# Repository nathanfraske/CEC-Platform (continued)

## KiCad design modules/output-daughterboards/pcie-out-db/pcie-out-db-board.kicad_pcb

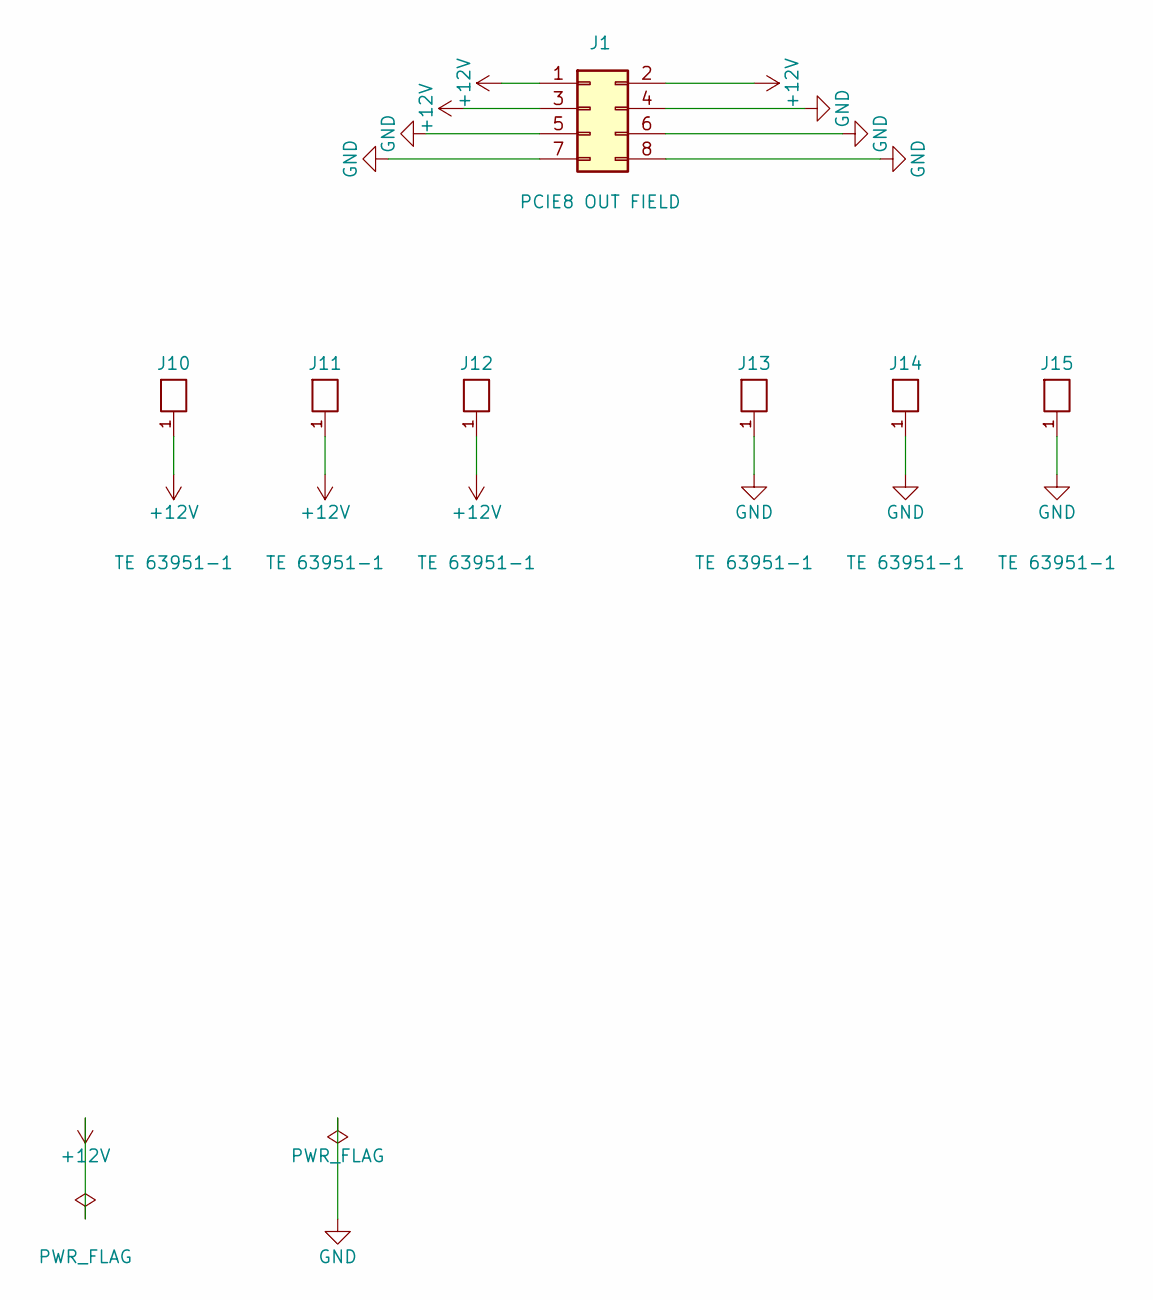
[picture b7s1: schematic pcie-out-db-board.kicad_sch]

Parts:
J1: PCIE8 OUT FIELD; PCIe8_Daughterboard_Field_P4.20mm
J10, J11, J12, J13, J14, J15: TE 63951-1; TE_63951-1_FASTON_Tab_250x032_RA_THT; MPN 63951-1; LCSC C591344

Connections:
+12V: J1.1, J1.2, J1.3, J10.1, J11.1, J12.1
GND: J1.4, J1.5, J1.6, J1.7, J1.8, J13.1, J14.1, J15.1

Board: 4 copper layers, 7 parts (0 on the bottom side), 2 nets, no tracks yet.

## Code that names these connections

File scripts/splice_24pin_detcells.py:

#!/usr/bin/env python3
# One-shot splice: add INA181A2 + TLV7011 fast-detection cells on the 24-pin's
# 3V3 and 5VSB rails, so all four rails carry the §6.13-style detection front end
# (owner 2026-07-07: "add the INA181 + comparator to the two remaining rails ...
# we are a total monitor anyway"). Mirrors the existing 12V/5V cells exactly
# (INA181A2 amp taps the same shunt Kelvin pair -> TLV7011 comparator vs the
# board-shared /THRESH -> a free MCU GPIO). Label-driven, like the flat sheet.
# Idempotent-guarded: refuses to run if the new refs already exist.
import sys, os, re
HERE = os.path.dirname(os.path.abspath(__file__))
sys.path.insert(0, HERE)
import cec_sch

SCH = os.path.join(HERE, "..", "modules", "atx-24pin-rev3", "24pin-module.kicad_sch")
PROJECT = "24pin-module"
ROOT = "a4774022-41d4-4be7-85b6-fed5477a3f9f"
GRID = 1.27

txt = open(SCH).read()

# ---- IC pin local geometry, carved from the file's own lib_symbols cache ----
def carve(t, i):
    d = 0
    for j in range(i, len(t)):
        if t[j] == '(':
            d += 1
        elif t[j] == ')':
            d -= 1
            if d == 0:
                return t[i:j+1]
    return None

def pins_of(libname):
    m = re.search(r'\(symbol "' + re.escape(libname) + r'"', txt)
    return cec_sch.pin_table(carve(txt, m.start()))

PIN = {
    "INA181": pins_of("cec-vendor:INA181A2IDBVR"),
    "TLV":    pins_of("cec-vendor:TLV7011DBVR"),
    "C":      pins_of("cec-vendor:C_Small"),
    "MCU":    pins_of("cec-vendor:ESP32-C6-MINI-1-N4"),
}

# ---- refs / placement ----
# Two cells, continuing the amp(x=294.64)/comp(x=364.49) column below the 5V cell.
CELLS = [
    dict(rail="3V3",  y=142.24, amp="U63V31",  comp="U73V31",  cap="C63V31",
         hi="SENSE3V3_HI",  lo="SENSE3V3_LO",  detamp="DETAMP3V3",  det="DET3V3",  mcu_pin="15"),
    dict(rail="5VSB", y=161.29, amp="U65VSB1", comp="U75VSB1", cap="C65VSB1",
         hi="SENSE5VSB_HI", lo="SENSE5VSB_LO", detamp="DETAMP5VSB", det="DET5VSB", mcu_pin="16"),
]
AMP_X, COMP_X, CAP_X = 294.64, 364.49, 323.85
FP_INA = "cec-Package_TO_SOT_SMD:SOT-23-6"
FP_TLV = "cec-Package_TO_SOT_SMD:SOT-23-5"
FP_C   = "cec-Capacitor_SMD:C_0402_1005Metric"

# idempotency guard
for c in CELLS:
    for r in (c["amp"], c["comp"], c["cap"]):
        if re.search(r'"' + re.escape(r) + r'"', txt):
            raise SystemExit(f"REFUSE: {r} already present -- splice already applied?")

pwr_n = [910]  # next #PWR number (max in file = 905)

def gsnap(v):
    return round(v / GRID) * GRID

def stub_and_target(ax, ay, ang, L=2.54):
    """Stub from a pin's abs connection point outward; return (endx,endy,labelang)."""
    if ang == 0:      # pin body extends +x, connection point on left -> outward -x
        return gsnap(ax - L), gsnap(ay), 180
    if ang == 180:    # outward +x
        return gsnap(ax + L), gsnap(ay), 0
    if ang == 270:    # cap top pin -> outward -y (up)
        return gsnap(ax), gsnap(ay - L), 90
    if ang == 90:     # cap bottom pin -> outward +y (down)
        return gsnap(ax), gsnap(ay + L), 270
    raise ValueError(ang)

out = []

def emit_ic(ref, lib, name, val, ox, oy, fp):
    """emit_symbol with COMPACT ref/value text (match the hand cells: ~above the part)."""
    s = cec_sch.emit_symbol(ref, lib, name, val, ox, oy, list(PIN_KEYS[name]),
                            PROJECT, ROOT, fp=fp)
    # relocate Reference (default y-15.24 -> y-10.16) and Value (y+15.24 -> y-7.62)
    s = s.replace(f'(at {cec_sch.f(ox)} {cec_sch.f(oy-15.24)} 0)',
                  f'(at {cec_sch.f(ox)} {cec_sch.f(oy-10.16)} 0)', 1)
    s = s.replace(f'(at {cec_sch.f(ox)} {cec_sch.f(oy+15.24)} 0)',
                  f'(at {cec_sch.f(ox)} {cec_sch.f(oy-7.62)} 0)', 1)
    out.append(s)

PIN_KEYS = {"INA181A2IDBVR": ["1","2","3","4","5","6"],
            "TLV7011DBVR":   ["1","2","3","4","5"],
            "C_Small":       ["1","2"]}

def wire_pin(part_pins, ref_placement_xy, pinnum, net_or_power):
    """Emit stub wire + a label (str net) or power symbol (('PWR', symname))."""
    ox, oy = ref_placement_xy
    lx, ly, ang, _len = part_pins[pinnum]
    ax, ay = ox + lx, oy - ly
    ex, ey, lang = stub_and_target(ax, ay, ang)
    out.append(cec_sch.emit_wire(ax, ay, ex, ey))
    if isinstance(net_or_power, tuple):
        _, symname = net_or_power
        ref = f"#PWR0{pwr_n[0]}"; pwr_n[0] += 1
        out.append(cec_sch.emit_global_power(symname, ex, ey, PROJECT, ROOT, ref))
    else:
        out.append(cec_sch.emit_label(net_or_power, ex, ey, lang))

for c in CELLS:
    y = c["y"]
    # --- INA181 amp ---
    emit_ic(c["amp"], "cec-vendor", "INA181A2IDBVR", "INA181A2IDBVR", AMP_X, y, FP_INA)
    ap = (AMP_X, y)
    wire_pin(PIN["INA181"], ap, "1", c["detamp"])          # OUT
    wire_pin(PIN["INA181"], ap, "2", ("PWR", "GND"))       # GND
    wire_pin(PIN["INA181"], ap, "3", c["hi"])              # IN+  shunt HI
    wire_pin(PIN["INA181"], ap, "4", c["lo"])              # IN-  shunt LO (Kelvin)
    wire_pin(PIN["INA181"], ap, "5", ("PWR", "GND"))       # REF -> GND (unidir)
    wire_pin(PIN["INA181"], ap, "6", ("PWR", "+3V3"))      # VS
    # --- bypass cap ---
    emit_ic(c["cap"], "cec-vendor", "C_Small", "100n", CAP_X, y, FP_C)
    cp = (CAP_X, y)
    wire_pin(PIN["C"], cp, "1", ("PWR", "+3V3"))
    wire_pin(PIN["C"], cp, "2", ("PWR", "GND"))
    # --- TLV7011 comparator ---
    emit_ic(c["comp"], "cec-vendor", "TLV7011DBVR", "TLV7011DBVR", COMP_X, y, FP_TLV)
    tp = (COMP_X, y)
    wire_pin(PIN["TLV"], tp, "1", c["det"])                # OUT -> MCU GPIO
    wire_pin(PIN["TLV"], tp, "2", ("PWR", "GND"))          # GND
    wire_pin(PIN["TLV"], tp, "3", c["detamp"])             # IN+ = amp OUT
    wire_pin(PIN["TLV"], tp, "4", "THRESH")                # IN- = shared threshold
    wire_pin(PIN["TLV"], tp, "5", ("PWR", "+3V3"))         # VCC

# --- MCU DET stubs (U1 at 275.59,204.47 rot0) ---
MCU_XY = (275.59, 204.47)
for c in CELLS:
    lx, ly, ang, _l = PIN["MCU"][c["mcu_pin"]]
    ax, ay = MCU_XY[0] + lx, MCU_XY[1] - ly
    ex, ey, lang = stub_and_target(ax, ay, ang)
    out.append(cec_sch.emit_wire(ax, ay, ex, ey))
    out.append(cec_sch.emit_label(c["det"], ex, ey, lang))

blob = "\n".join(out) + "\n"
# splice before the final (sheet_instances ...)
idx = txt.rindex("\t(sheet_instances")
new = txt[:idx] + blob + txt[idx:]
open(SCH, "w").write(new)
print(f"spliced {len(out)} s-expr elements; file {len(txt)} -> {len(new)} bytes")
